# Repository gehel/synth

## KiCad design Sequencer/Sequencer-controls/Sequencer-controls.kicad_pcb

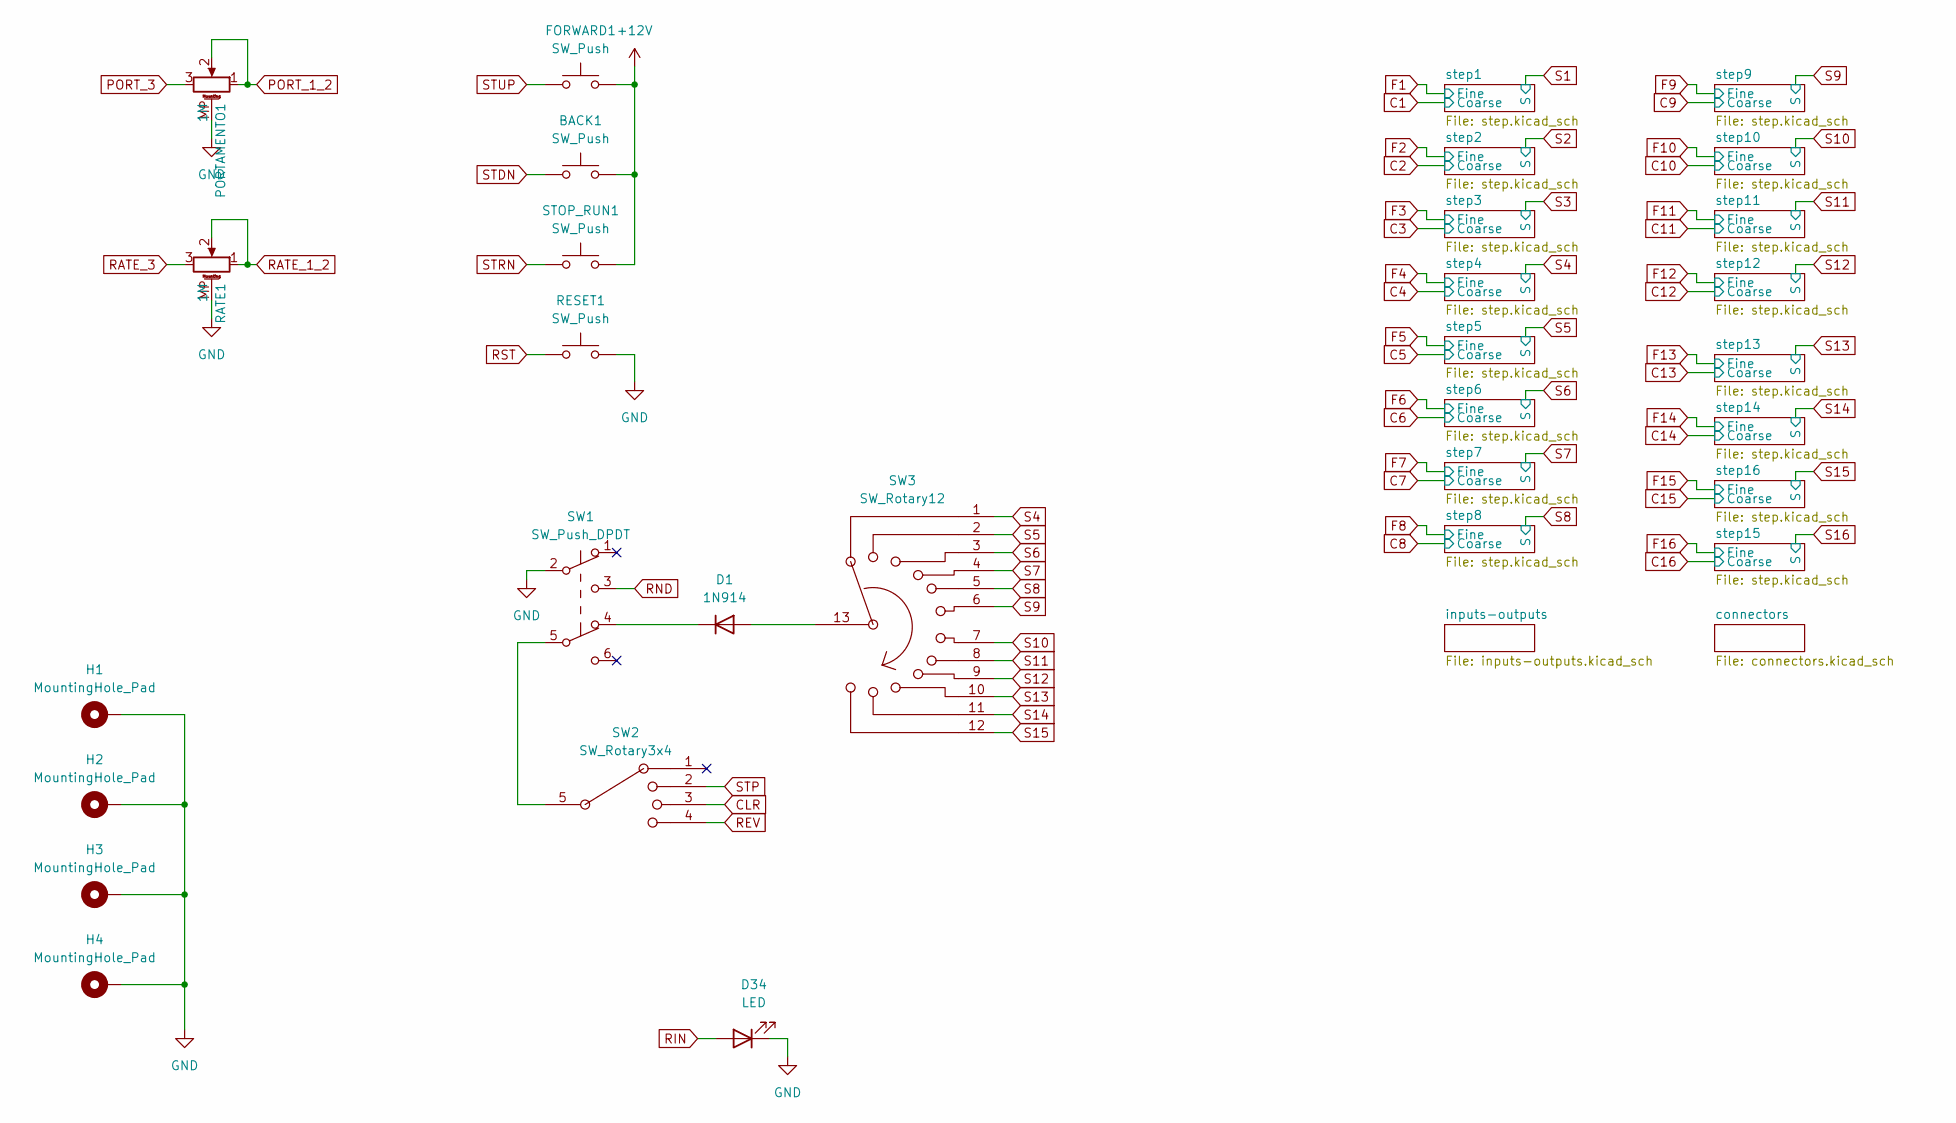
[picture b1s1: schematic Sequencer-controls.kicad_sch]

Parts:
BACK1: SW_Push; SW_PUSH_6mm
D1: 1N914; D_DO-35_SOD27_P7.62mm_Horizontal
D34: LED; LED_D3.0mm
FORWARD1: SW_Push; SW_PUSH_6mm
H1, H2, H3, H4: MountingHole_Pad; MountingHole_3.2mm_M3_Pad
PORTAMENTO1: 1M; Potentiometer_Bourns_PTV09A-1_Single_Vertical
RATE1: 1M; Potentiometer_Bourns_PTV09A-1_Single_Vertical
RESET1: SW_Push; SW_PUSH_6mm
STOP_RUN1: SW_Push; SW_PUSH_6mm
SW1: SW_Push_DPDT; ToggleSwitch_MTS-202_DPDT
SW2: SW_Rotary3x4; rotary_switch_3P4T
SW3: SW_Rotary12; rotary_switch_1P12T

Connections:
+12V: BACK1.2, FORWARD1.2, STOP_RUN1.2; also elsewhere on the board
CLR: SW2.3; also elsewhere on the board
GND: D34.1 (K), H1.1, H2.1, H3.1, H4.1, PORTAMENTO1.MP (MountPin), RATE1.MP (MountPin), RESET1.2, SW1.2 (B); also elsewhere on the board
unnamed: D1.2 (A), SW3.13
unnamed: D1.1 (K), SW1.4 (A)
unnamed: SW1.5 (B), SW2.5
PORT_1_2: PORTAMENTO1.1, PORTAMENTO1.2; also elsewhere on the board
PORT_3: PORTAMENTO1.3; also elsewhere on the board
RATE_1_2: RATE1.1, RATE1.2; also elsewhere on the board
RATE_3: RATE1.3; also elsewhere on the board
REV: SW2.4; also elsewhere on the board
RIN: D34.2 (A); also elsewhere on the board
RND: SW1.3 (C); also elsewhere on the board
RST: RESET1.1; also elsewhere on the board
S4: SW3.1; also elsewhere on the board
S5: SW3.2; also elsewhere on the board
S6: SW3.3; also elsewhere on the board
S7: SW3.4; also elsewhere on the board
S8: SW3.5; also elsewhere on the board
S9: SW3.6; also elsewhere on the board
S10: SW3.7; also elsewhere on the board
S11: SW3.8; also elsewhere on the board
S12: SW3.9; also elsewhere on the board
S13: SW3.10; also elsewhere on the board
S14: SW3.11; also elsewhere on the board
STDN: BACK1.1; also elsewhere on the board
STP: SW2.2; also elsewhere on the board
STRN: STOP_RUN1.1; also elsewhere on the board
STUP: FORWARD1.1; also elsewhere on the board

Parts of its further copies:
D11: LED; LED_D3.0mm

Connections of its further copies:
CBUS: D11.1 (K); also elsewhere on the board
S5: D11.2 (A); also elsewhere on the board

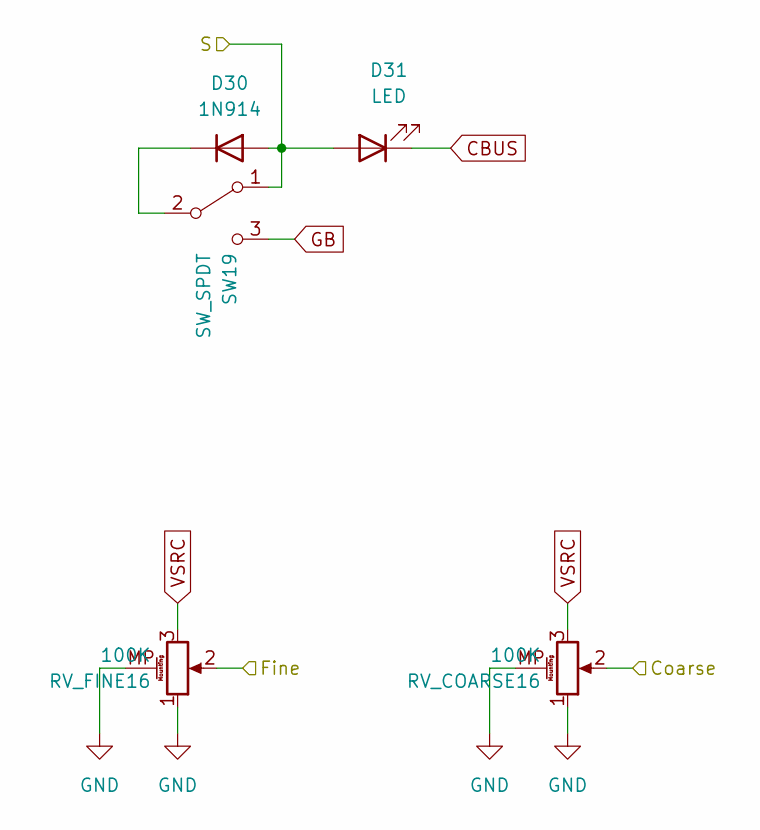
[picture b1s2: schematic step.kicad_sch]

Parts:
D30: 1N914; D_DO-35_SOD27_P7.62mm_Horizontal
D31: LED; LED_D3.0mm
RV_COARSE16: 100K; Potentiometer_Bourns_PTV09A-1_Single_Vertical
RV_FINE16: 100K; Potentiometer_Bourns_PTV09A-1_Single_Vertical
SW19: SW_SPDT; ToggleSwitch_MTS-102_SPDT

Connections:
C16: RV_COARSE16.2; also elsewhere on the board
CBUS: D31.1 (K); also elsewhere on the board
F16: RV_FINE16.2; also elsewhere on the board
GB: SW19.3 (C); also elsewhere on the board
GND: RV_COARSE16.1, RV_COARSE16.MP (MountPin), RV_FINE16.1, RV_FINE16.MP (MountPin); also elsewhere on the board
VSRC: RV_COARSE16.3, RV_FINE16.3; also elsewhere on the board

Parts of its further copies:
D2, D4, D6, D8, D10, D12, D14, D16, D18, D20, D22, D24, D26, D28, D32: 1N914; D_DO-35_SOD27_P7.62mm_Horizontal
D3, D5, D7, D9, D11, D13, D15, D17, D19, D21, D23, D25, D27, D29, D33: LED; LED_D3.0mm
RV_COARSE1, RV_COARSE2, RV_COARSE3, RV_COARSE4, RV_COARSE5, RV_COARSE6, RV_COARSE7, RV_COARSE8, RV_COARSE9, RV_COARSE10, RV_COARSE11, RV_COARSE12, RV_COARSE13, RV_COARSE14, RV_COARSE15: 100K; Potentiometer_Bourns_PTV09A-1_Single_Vertical
RV_FINE1, RV_FINE2, RV_FINE3, RV_FINE4, RV_FINE5, RV_FINE6, RV_FINE7, RV_FINE8, RV_FINE9, RV_FINE10, RV_FINE11, RV_FINE12, RV_FINE13, RV_FINE14, RV_FINE15: 100K; Potentiometer_Bourns_PTV09A-1_Single_Vertical
SW4, SW5, SW6, SW7, SW8, SW9, SW10, SW11, SW12, SW13, SW14, SW15, SW16, SW17, SW18: SW_SPDT; ToggleSwitch_MTS-102_SPDT

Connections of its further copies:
C1: RV_COARSE1.2; also elsewhere on the board
C2: RV_COARSE2.2; also elsewhere on the board
C3: RV_COARSE3.2; also elsewhere on the board
C4: RV_COARSE4.2; also elsewhere on the board
C5: RV_COARSE5.2; also elsewhere on the board
C6: RV_COARSE6.2; also elsewhere on the board
C7: RV_COARSE7.2; also elsewhere on the board
C8: RV_COARSE8.2; also elsewhere on the board
C9: RV_COARSE9.2; also elsewhere on the board
C10: RV_COARSE10.2; also elsewhere on the board
C11: RV_COARSE11.2; also elsewhere on the board
C12: RV_COARSE12.2; also elsewhere on the board
C13: RV_COARSE13.2; also elsewhere on the board
C14: RV_COARSE14.2; also elsewhere on the board
C15: RV_COARSE15.2; also elsewhere on the board
CBUS: D3.1 (K), D5.1 (K), D7.1 (K), D9.1 (K), D11.1 (K), D13.1 (K), D15.1 (K), D17.1 (K), D19.1 (K), D21.1 (K), D23.1 (K), D25.1 (K), D27.1 (K), D29.1 (K), D33.1 (K); also elsewhere on the board
F1: RV_FINE1.2; also elsewhere on the board
F2: RV_FINE2.2; also elsewhere on the board
F3: RV_FINE3.2; also elsewhere on the board
F4: RV_FINE4.2; also elsewhere on the board
F5: RV_FINE5.2; also elsewhere on the board
F6: RV_FINE6.2; also elsewhere on the board
F7: RV_FINE7.2; also elsewhere on the board
F8: RV_FINE8.2; also elsewhere on the board
F9: RV_FINE9.2; also elsewhere on the board
F10: RV_FINE10.2; also elsewhere on the board
F11: RV_FINE11.2; also elsewhere on the board
F12: RV_FINE12.2; also elsewhere on the board
F13: RV_FINE13.2; also elsewhere on the board
F14: RV_FINE14.2; also elsewhere on the board
F15: RV_FINE15.2; also elsewhere on the board
GB: SW4.3 (C), SW5.3 (C), SW6.3 (C), SW7.3 (C), SW8.3 (C), SW9.3 (C), SW10.3 (C), SW11.3 (C), SW12.3 (C), SW13.3 (C), SW14.3 (C), SW15.3 (C), SW16.3 (C), SW17.3 (C), SW18.3 (C); also elsewhere on the board
GND: RV_COARSE1.1, RV_COARSE1.MP (MountPin), RV_COARSE2.1, RV_COARSE2.MP (MountPin), RV_COARSE3.1, RV_COARSE3.MP (MountPin), RV_COARSE4.1, RV_COARSE4.MP (MountPin), RV_COARSE5.1, RV_COARSE5.MP (MountPin), RV_COARSE6.1, RV_COARSE6.MP (MountPin), RV_COARSE7.1, RV_COARSE7.MP (MountPin), RV_COARSE8.1, RV_COARSE8.MP (MountPin), RV_COARSE9.1, RV_COARSE9.MP (MountPin), RV_COARSE10.1, RV_COARSE10.MP (MountPin), RV_COARSE11.1, RV_COARSE11.MP (MountPin), RV_COARSE12.1, RV_COARSE12.MP (MountPin), RV_COARSE13.1, RV_COARSE13.MP (MountPin), RV_COARSE14.1, RV_COARSE14.MP (MountPin), RV_COARSE15.1, RV_COARSE15.MP (MountPin), RV_FINE1.1, RV_FINE1.MP (MountPin), RV_FINE2.1, RV_FINE2.MP (MountPin), RV_FINE3.1, RV_FINE3.MP (MountPin), RV_FINE4.1, RV_FINE4.MP (MountPin), RV_FINE5.1, RV_FINE5.MP (MountPin), RV_FINE6.1, RV_FINE6.MP (MountPin), RV_FINE7.1, RV_FINE7.MP (MountPin), RV_FINE8.1, RV_FINE8.MP (MountPin), RV_FINE9.1, RV_FINE9.MP (MountPin), RV_FINE10.1, RV_FINE10.MP (MountPin), RV_FINE11.1, RV_FINE11.MP (MountPin), RV_FINE12.1, RV_FINE12.MP (MountPin), RV_FINE13.1, RV_FINE13.MP (MountPin), RV_FINE14.1, RV_FINE14.MP (MountPin), RV_FINE15.1, RV_FINE15.MP (MountPin); also elsewhere on the board
unnamed: D2.1 (K), SW4.2 (B)
unnamed: D4.1 (K), SW5.2 (B)
unnamed: D6.1 (K), SW6.2 (B)
unnamed: D8.1 (K), SW7.2 (B)
unnamed: D10.1 (K), SW8.2 (B)
unnamed: D12.1 (K), SW9.2 (B)
unnamed: D14.1 (K), SW10.2 (B)
unnamed: D16.1 (K), SW11.2 (B)
unnamed: D18.1 (K), SW12.2 (B)
unnamed: D20.1 (K), SW13.2 (B)
unnamed: D22.1 (K), SW14.2 (B)
unnamed: D24.1 (K), SW15.2 (B)
unnamed: D26.1 (K), SW16.2 (B)
unnamed: D28.1 (K), SW17.2 (B)
S1: D2.2 (A), D3.2 (A), SW4.1 (A); also elsewhere on the board
S2: D4.2 (A), D5.2 (A), SW5.1 (A); also elsewhere on the board
S3: D6.2 (A), D7.2 (A), SW6.1 (A); also elsewhere on the board
S4: D8.2 (A), D9.2 (A), SW7.1 (A); also elsewhere on the board
S5: D10.2 (A), D11.2 (A), SW8.1 (A); also elsewhere on the board
S6: D12.2 (A), D13.2 (A), SW9.1 (A); also elsewhere on the board
S7: D14.2 (A), D15.2 (A), SW10.1 (A); also elsewhere on the board
S8: D16.2 (A), D17.2 (A), SW11.1 (A); also elsewhere on the board
S9: D18.2 (A), D19.2 (A), SW12.1 (A); also elsewhere on the board
S10: D20.2 (A), D21.2 (A), SW13.1 (A); also elsewhere on the board
S11: D22.2 (A), D23.2 (A), SW14.1 (A); also elsewhere on the board
S12: D24.2 (A), D25.2 (A), SW15.1 (A); also elsewhere on the board
S13: D26.2 (A), D27.2 (A), SW16.1 (A); also elsewhere on the board
S14: D28.2 (A), D29.2 (A), SW17.1 (A); also elsewhere on the board
VSRC: RV_COARSE1.3, RV_COARSE2.3, RV_COARSE3.3, RV_COARSE4.3, RV_COARSE5.3, RV_COARSE6.3, RV_COARSE7.3, RV_COARSE8.3, RV_COARSE9.3, RV_COARSE10.3, RV_COARSE11.3, RV_COARSE12.3, RV_COARSE13.3, RV_COARSE14.3, RV_COARSE15.3, RV_FINE1.3, RV_FINE2.3, RV_FINE3.3, RV_FINE4.3, RV_FINE5.3, RV_FINE6.3, RV_FINE7.3, RV_FINE8.3, RV_FINE9.3, RV_FINE10.3, RV_FINE11.3, RV_FINE12.3, RV_FINE13.3, RV_FINE14.3, RV_FINE15.3; also elsewhere on the board

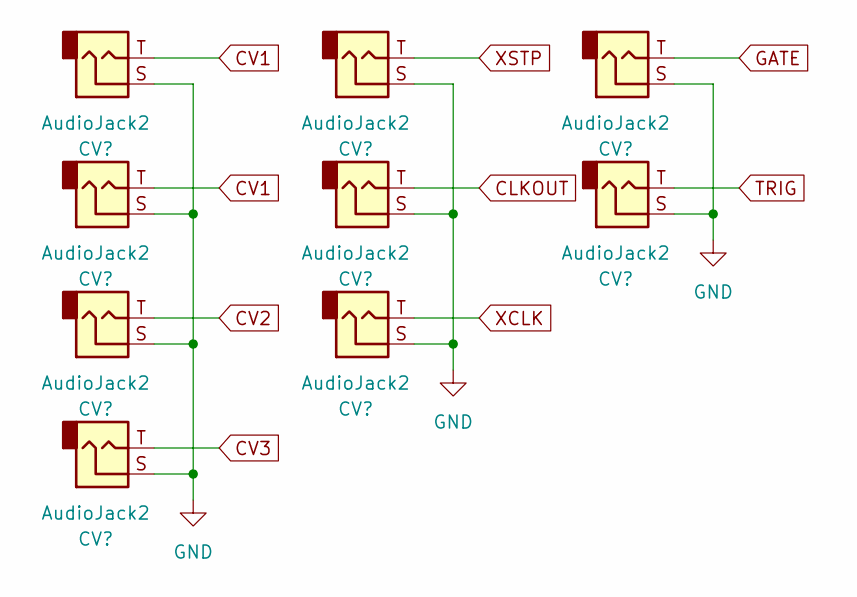
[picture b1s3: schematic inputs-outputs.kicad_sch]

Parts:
CLKOUT1: AudioJack2; Jack_3.5mm_QingPu_WQP-PJ398SM_Vertical_CircularHoles
CV1, CV2, CV3, CV4: AudioJack2; Jack_3.5mm_QingPu_WQP-PJ398SM_Vertical_CircularHoles
GATE1: AudioJack2; Jack_3.5mm_QingPu_WQP-PJ398SM_Vertical_CircularHoles
TRIG1: AudioJack2; Jack_3.5mm_QingPu_WQP-PJ398SM_Vertical_CircularHoles
XCLK1: AudioJack2; Jack_3.5mm_QingPu_WQP-PJ398SM_Vertical_CircularHoles
XSTP1: AudioJack2; Jack_3.5mm_QingPu_WQP-PJ398SM_Vertical_CircularHoles

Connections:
CLKOUT: CLKOUT1.T; also elsewhere on the board
CV1: CV1.T, CV2.T; also elsewhere on the board
CV2: CV3.T; also elsewhere on the board
CV3: CV4.T; also elsewhere on the board
GATE: GATE1.T; also elsewhere on the board
GND: CLKOUT1.S, CV1.S, CV2.S, CV3.S, CV4.S, GATE1.S, TRIG1.S, XCLK1.S, XSTP1.S; also elsewhere on the board
TRIG: TRIG1.T; also elsewhere on the board
XCLK: XCLK1.T; also elsewhere on the board
XSTP: XSTP1.T; also elsewhere on the board

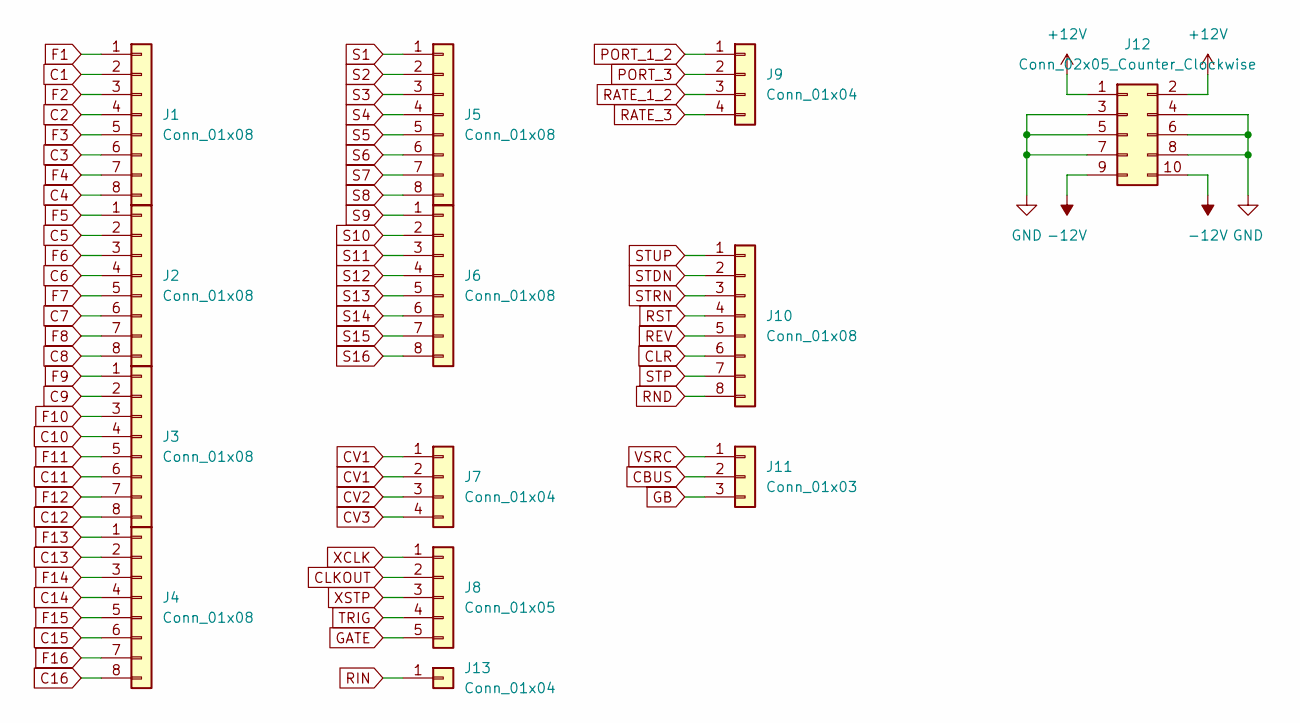
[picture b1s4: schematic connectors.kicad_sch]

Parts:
J1, J2, J3, J4, J5, J6, J10: Conn_01x08; PinHeader_1x08_P2.54mm_Vertical
J7, J9: Conn_01x04; PinHeader_1x04_P2.54mm_Vertical
J8: Conn_01x05; PinHeader_1x05_P2.54mm_Vertical
J11: Conn_01x03; PinHeader_1x03_P2.54mm_Vertical
J12: Conn_02x05_Counter_Clockwise; PinHeader_2x05_P2.54mm_Vertical
J13: Conn_01x04; PinHeader_1x01_P2.54mm_Vertical

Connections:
+12V: J12.1, J12.2; also elsewhere on the board
-12V: J12.9, J12.10
C1: J1.2; also elsewhere on the board
C2: J1.4; also elsewhere on the board
C3: J1.6; also elsewhere on the board
C4: J1.8; also elsewhere on the board
C5: J2.2; also elsewhere on the board
C6: J2.4; also elsewhere on the board
C7: J2.6; also elsewhere on the board
C8: J2.8; also elsewhere on the board
C9: J3.2; also elsewhere on the board
C10: J3.4; also elsewhere on the board
C11: J3.6; also elsewhere on the board
C12: J3.8; also elsewhere on the board
C13: J4.2; also elsewhere on the board
C14: J4.4; also elsewhere on the board
C15: J4.6; also elsewhere on the board
C16: J4.8; also elsewhere on the board
CBUS: J11.2; also elsewhere on the board
CLKOUT: J8.2; also elsewhere on the board
CLR: J10.6; also elsewhere on the board
CV1: J7.1, J7.2; also elsewhere on the board
CV2: J7.3; also elsewhere on the board
CV3: J7.4; also elsewhere on the board
F1: J1.1; also elsewhere on the board
F2: J1.3; also elsewhere on the board
F3: J1.5; also elsewhere on the board
F4: J1.7; also elsewhere on the board
F5: J2.1; also elsewhere on the board
F6: J2.3; also elsewhere on the board
F7: J2.5; also elsewhere on the board
F8: J2.7; also elsewhere on the board
F9: J3.1; also elsewhere on the board
F10: J3.3; also elsewhere on the board
F11: J3.5; also elsewhere on the board
F12: J3.7; also elsewhere on the board
F13: J4.1; also elsewhere on the board
F14: J4.3; also elsewhere on the board
F15: J4.5; also elsewhere on the board
F16: J4.7; also elsewhere on the board
GATE: J8.5; also elsewhere on the board
GB: J11.3; also elsewhere on the board
GND: J12.3, J12.4, J12.5, J12.6, J12.7, J12.8; also elsewhere on the board
PORT_1_2: J9.1; also elsewhere on the board
PORT_3: J9.2; also elsewhere on the board
RATE_1_2: J9.3; also elsewhere on the board
RATE_3: J9.4; also elsewhere on the board
REV: J10.5; also elsewhere on the board
RND: J10.8; also elsewhere on the board
RST: J10.4; also elsewhere on the board
S1: J5.1; also elsewhere on the board
S2: J5.2; also elsewhere on the board
S3: J5.3; also elsewhere on the board
S4: J5.4; also elsewhere on the board
S5: J5.5; also elsewhere on the board
S6: J5.6; also elsewhere on the board
S7: J5.7; also elsewhere on the board
S8: J5.8; also elsewhere on the board
S9: J6.1; also elsewhere on the board
S10: J6.2; also elsewhere on the board
S11: J6.3; also elsewhere on the board
S12: J6.4; also elsewhere on the board
S13: J6.5; also elsewhere on the board
S14: J6.6; also elsewhere on the board
STDN: J10.2; also elsewhere on the board
STP: J10.7; also elsewhere on the board
STRN: J10.3; also elsewhere on the board
STUP: J10.1; also elsewhere on the board
TRIG: J8.4; also elsewhere on the board
VSRC: J11.1; also elsewhere on the board
XCLK: J8.1; also elsewhere on the board
XSTP: J8.3; also elsewhere on the board

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
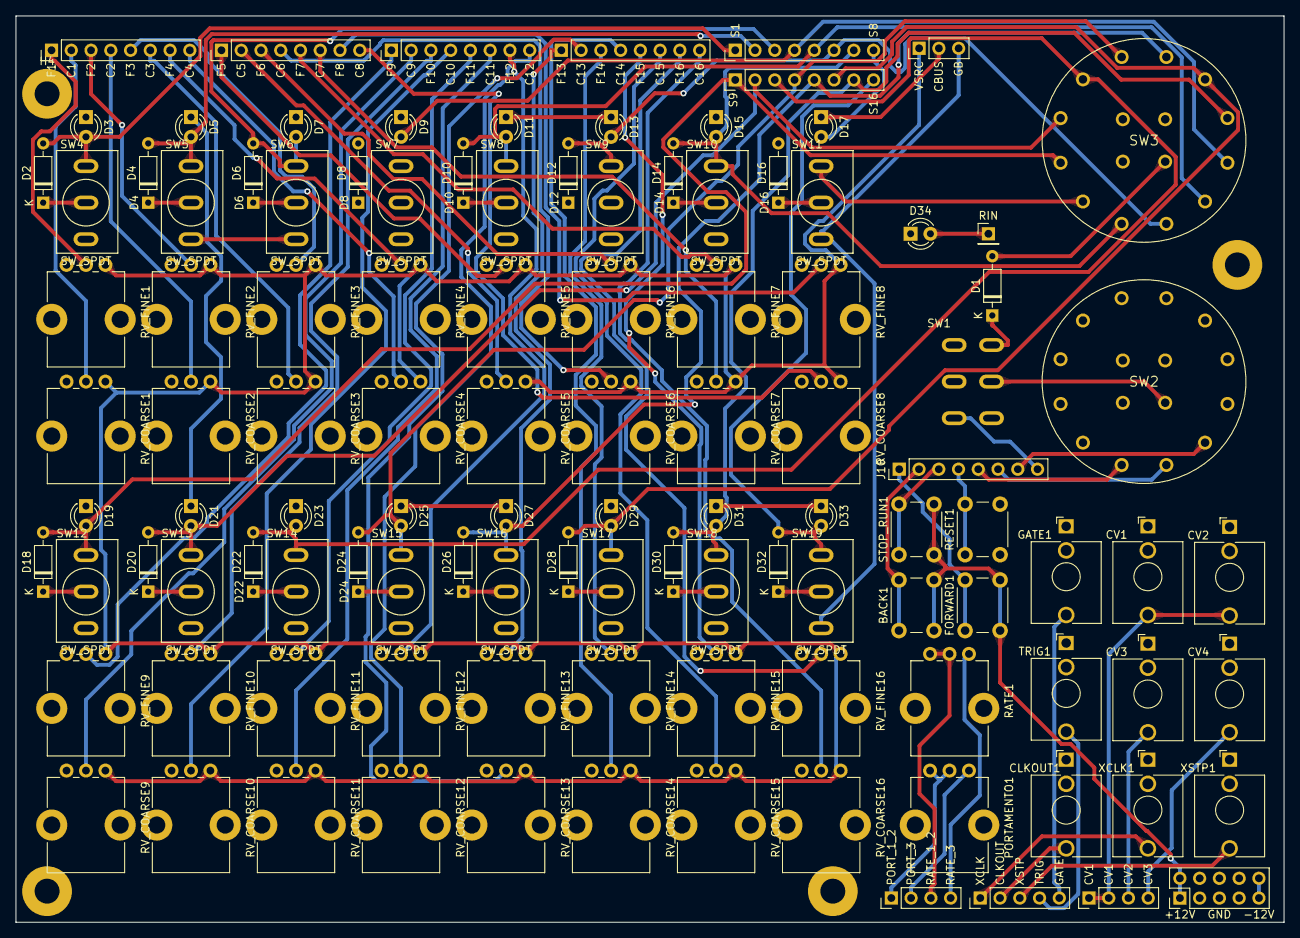
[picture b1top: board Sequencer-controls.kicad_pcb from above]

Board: 4 copper layers, 163.0 x 116.5 mm, 117 parts (0 on the bottom side), 94 nets.

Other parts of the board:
RIN: Conn_01x04; PinHeader_1x01_P2.54mm_Vertical

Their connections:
RIN: RIN.1; also elsewhere on the board

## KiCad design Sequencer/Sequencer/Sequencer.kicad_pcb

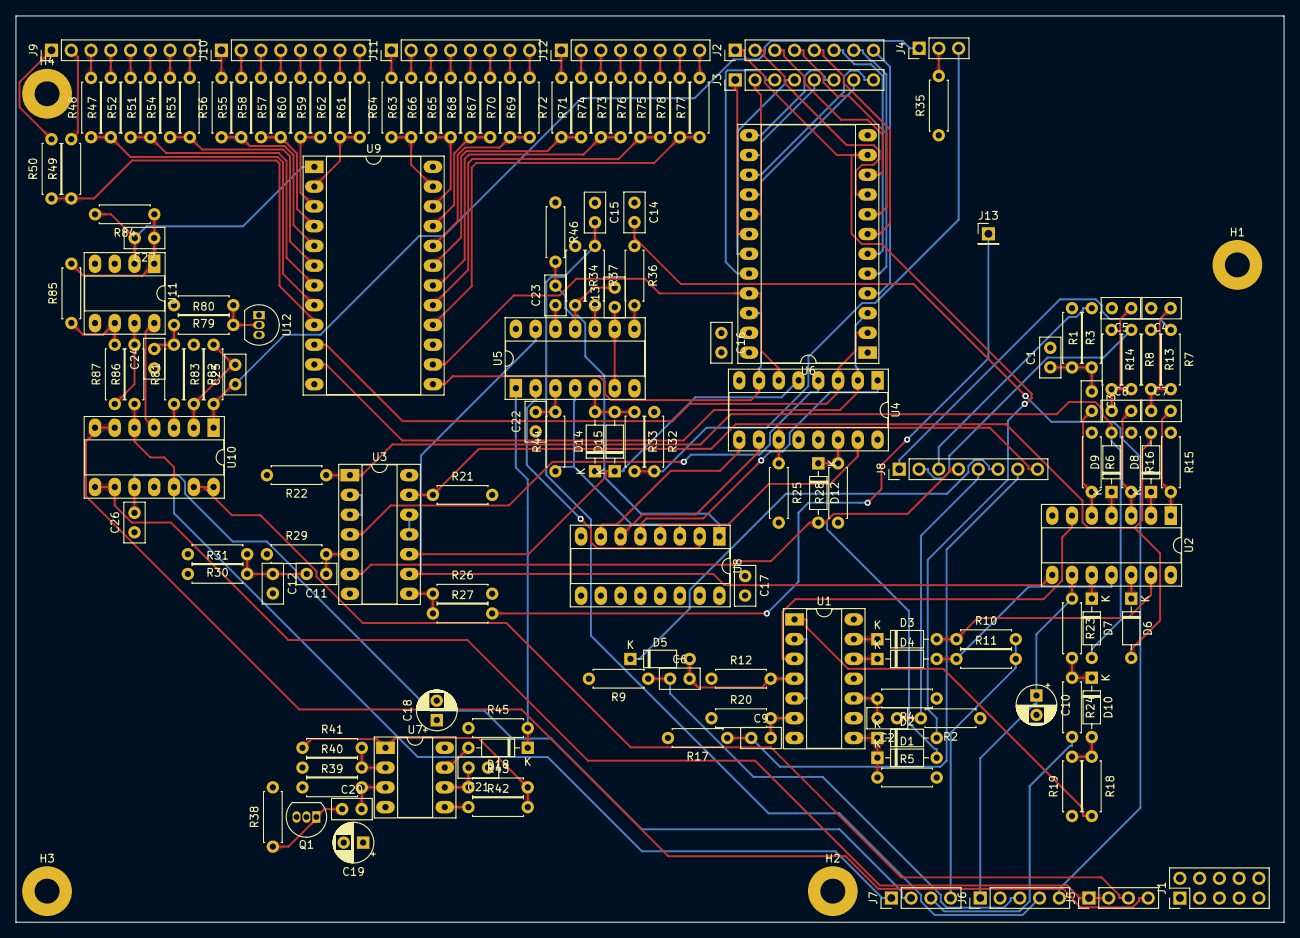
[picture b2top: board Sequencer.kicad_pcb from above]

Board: 4 copper layers, 163.0 x 116.5 mm, 158 parts (0 on the bottom side), 157 nets.

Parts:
C1, C4, C5, C6, C9, C12, C20, C21: 10nF; C_Disc_D5.0mm_W2.5mm_P2.50mm
C2, C3, C7, C8, C11: 20nF; C_Disc_D5.0mm_W2.5mm_P2.50mm
C10: 1uF; CP_Radial_D5.0mm_P2.50mm
C13, C14, C15, C22: 1nF; C_Disc_D5.0mm_W2.5mm_P2.50mm
C16, C17, C24, C26: 100nF; C_Disc_D5.0mm_W2.5mm_P2.50mm
C18, C19: 10uF; CP_Radial_D5.0mm_P2.50mm
C23: 100pF; C_Disc_D5.0mm_W2.5mm_P2.50mm
C25, C27: 470pF; C_Disc_D5.0mm_W2.5mm_P2.50mm
D1, D2, D3, D4, D5, D6, D7, D8, D9, D10, D12, D14, D15, D18: 1N914; D_DO-35_SOD27_P7.62mm_Horizontal
H1, H2, H3, H4: MountingHole_Pad; MountingHole_3.2mm_M3_Pad
J1: Conn_02x05_Odd_Even; PinHeader_2x05_P2.54mm_Vertical
J2, J3, J8, J9, J10, J11, J12: Conn_01x08; PinHeader_1x08_P2.54mm_Vertical
J4: Conn_01x03; PinHeader_1x03_P2.54mm_Vertical
J5, J7: Conn_01x04; PinHeader_1x04_P2.54mm_Vertical
J6: Conn_01x05; PinHeader_1x05_P2.54mm_Vertical
J13: Conn_01x04; PinHeader_1x01_P2.54mm_Vertical
Q1: 2N3904; TO-92_Inline
R1, R5, R7, R8, R10, R11, R31, R79, R85, R87: 10K; R_Axial_DIN0207_L6.3mm_D2.5mm_P7.62mm_Horizontal
R2, R4, R6, R15, R16, R29: 220K; R_Axial_DIN0207_L6.3mm_D2.5mm_P7.62mm_Horizontal
R3, R13, R14, R30: 680K; R_Axial_DIN0207_L6.3mm_D2.5mm_P7.62mm_Horizontal
R9, R12, R17, R20, R33, R34, R42, R47, R49, R51, R53, R55, R57, R59, R61, R63, R65, R67, R69, R71, R73, R75, R77, R82, R84: 100K; R_Axial_DIN0207_L6.3mm_D2.5mm_P7.62mm_Horizontal
R18, R26, R36, R37: 1K; R_Axial_DIN0207_L6.3mm_D2.5mm_P7.62mm_Horizontal
R19: 3.9K; R_Axial_DIN0207_L6.3mm_D2.5mm_P7.62mm_Horizontal
R21, R22, R25, R28, R80, R81: 47K; R_Axial_DIN0207_L6.3mm_D2.5mm_P7.62mm_Horizontal
R23: 6.2K; R_Axial_DIN0207_L6.3mm_D2.5mm_P7.62mm_Horizontal
R24: 20K; R_Axial_DIN0207_L6.3mm_D2.5mm_P7.62mm_Horizontal
R27, R35: 3K; R_Axial_DIN0207_L6.3mm_D2.5mm_P7.62mm_Horizontal
R32, R40, R45, R46: 4.7K; R_Axial_DIN0207_L6.3mm_D2.5mm_P7.62mm_Horizontal
R38, R39, R48, R50, R52, R54, R56, R58, R60, R62, R64, R66, R68, R70, R72, R74, R76, R78: 2M; R_Axial_DIN0207_L6.3mm_D2.5mm_P7.62mm_Horizontal
R41: 4.7M; R_Axial_DIN0207_L6.3mm_D2.5mm_P7.62mm_Horizontal
R43, R44: 1M; R_Axial_DIN0207_L6.3mm_D2.5mm_P7.62mm_Horizontal
R83: 200K; R_Axial_DIN0207_L6.3mm_D2.5mm_P7.62mm_Horizontal
R86: 22R; R_Axial_DIN0207_L6.3mm_D2.5mm_P7.62mm_Horizontal
U1: 4013; DIP-14_W7.62mm_Socket_LongPads
U2, U3, U5: 40106; DIP-14_W7.62mm_Socket_LongPads
U4: 40193; DIP-16_W7.62mm_Socket_LongPads
U6: 4514; DIP-24_W15.24mm_Socket_LongPads
U7, U11: TL072; DIP-8_W7.62mm_Socket_LongPads
U8: CD4094; DIP-16_W7.62mm_Socket_LongPads
U9: CD74HC4067M; DIP-24_W15.24mm_Socket_LongPads
U10: TL074; DIP-14_W7.62mm_Socket_LongPads
U12: LM285Z-ADJ; TO-92_Inline

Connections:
+12V: C16.2, C17.2, C18.1, J1.1, J1.2, R21.2, R22.2, R25.2, R29.1, R30.2, R34.1, R38.2, R79.2, U1.14 (VDD), U2.14 (VDD), U3.14 (VDD), U4.16 (VDD), U5.14 (VDD), U6.1 (EL), U6.24 (Vdd), U7.8 (V+), U8.15 (ENA), U8.16 (VDD), U9.24 (VCC), U10.4 (V+), U11.8 (V+)
-12V: C19.2, J1.9, J1.10, Q1.2 (B), U7.4 (V-), U10.11 (V-), U11.4 (V-)
C1: J9.2, R49.2
C2: J9.4, R47.2
C3: J9.6, R51.2
C4: J9.8, R53.2
C5: J10.2, R55.2
C6: J10.4, R57.2
C7: J10.6, R59.2
C8: J10.8, R61.2
C9: J11.2, R63.2
C10: J11.4, R65.2
C11: J11.6, R67.2
C12: J11.8, R69.2
C13: J12.2, R71.2
C14: J12.4, R73.2
C15: J12.6, R75.2
C16: J12.8, R77.2
CBUS: J4.2, R35.2
CLK: J7.4, R10.2, R11.2, U2.8, U3.9, U5.13
CLR: D5.1 (K), J8.6
CV1: J5.1, J5.2, U10.8, U10.9 (-)
CV2: J5.3, U10.13 (-), U10.14
CV3: J5.4, U10.6 (-), U10.7
DA: U4.15 (P0), U8.4 (Q1)
DB: U4.1, U8.5 (Q2)
DC: U4.10 (P2), U8.6 (Q3)
DD: U4.9 (P3), U8.7 (Q4)
DOWN: U3.4, U4.4 (DOWN)
F1: J9.1, R50.2
F2: J9.3, R48.2
F3: J9.5, R52.2
F4: J9.7, R54.2
F5: J10.1, R56.2
F6: J10.3, R58.2
F7: J10.5, R60.2
F8: J10.7, R62.2
F9: J11.1, R64.2
F10: J11.3, R66.2
F11: J11.5, R68.2
F12: J11.7, R70.2
F13: J12.1, R72.2
F14: J12.3, R74.2
F15: J12.5, R76.2
F16: J12.7, R78.2
FR1: R49.1, R50.1, U9.9 (I0)
FR2: R47.1, R48.1, U9.8 (I1)
FR3: R51.1, R52.1, U9.7 (I2)
FR4: R53.1, R54.1, U9.6 (I3)
FR5: R55.1, R56.1, U9.5 (I4)
FR6: R57.1, R58.1, U9.4 (I5)
FR7: R59.1, R60.1, U9.3 (I6)
FR8: R61.1, R62.1, U9.2 (I7)
FR9: R63.1, R64.1, U9.23 (I8)
FR10: R65.1, R66.1, U9.22 (I9)
FR11: R67.1, R68.1, U9.21 (I10)
FR12: R69.1, R70.1, U9.20 (I11)
FR13: R71.1, R72.1, U9.19 (I12)
FR14: R73.1, R74.1, U9.18 (I13)
FR15: R75.1, R76.1, U9.17 (I14)
FR16: R77.1, R78.1, U9.16 (I15)
FWD: D2.2 (A), J2.1, U6.11 (Q0)
GATE: C14.2, J6.5, R36.1
GB: J4.3, R32.2, R33.2
GND: C1.2, C4.2, C5.2, C10.2, C12.2, C14.1, C15.1, C16.1, C17.1, C18.2, C19.1, C21.1, C22.1, C24.1, C26.1, H1.1, H2.1, H3.1, H4.1, J1.3, J1.4, J1.5, J1.6, J1.7, J1.8, R2.1, R3.1, R4.1, R5.2, R6.1, R9.2, R12.1, R13.1, R14.1, R15.1, R16.1, R17.2, R19.1, R20.1, R28.1, R32.1, R35.1, R39.1, R40.1, R45.1, R46.1, R82.1, U1.7 (VSS), U1.9 (D), U1.11 (C), U2.7 (VSS), U3.7 (VSS), U4.8 (VSS), U5.7 (VSS), U6.12 (Vss), U6.23 (~EN), U8.8 (VSS), U9.12 (GND), U9.15 (~E), U11.3 (+), U11.5 (+), U12.3 (A)
unnamed: C1.1, C3.1, R1.1, R3.2
unnamed: C3.2, R6.2, U2.5
unnamed: C4.1, C7.1, R7.2, R13.2
unnamed: C5.1, C8.1, R8.2, R14.2
unnamed: C7.2, R15.2, U2.1
unnamed: C8.2, R16.2, U2.3
unnamed: C11.1, R29.2, U3.5
unnamed: C11.2, C12.1, R30.1, R31.2
unnamed: C13.1, U5.6, U5.9
unnamed: C13.2, R34.2, U5.11
unnamed: C22.2, R44.2, U5.3
unnamed: C23.1, U5.12
unnamed: C24.2, R80.1, R81.2
unnamed: C27.1, R84.1, R85.2, U11.1
unnamed: D1.1 (K), D2.1 (K), R5.1, U1.8 (S)
unnamed: D3.2 (A), R10.1, U2.13
unnamed: D3.1 (K), U1.13 (Q)
unnamed: D4.2 (A), R11.1, U2.11
unnamed: D4.1 (K), U1.12 (~Q)
unnamed: C6.2, D5.2 (A), R12.2, U1.4 (R)
unnamed: D6.2 (A), D8.2 (A), R21.1, U3.13
unnamed: D6.1 (K), U2.12
unnamed: D7.2 (A), D9.2 (A), R22.1, U3.1
unnamed: D7.1 (K), U2.10
unnamed: D8.1 (K), U2.2
unnamed: D9.1 (K), U2.4
unnamed: D10.2 (A), R18.1, R19.2
unnamed: D10.1 (K), R23.2, R24.1
unnamed: D12.1 (K), R28.2, U4.14 (MR)
unnamed: D14.2 (A), D15.2 (A), R33.1, U5.5
unnamed: D18.2 (A), U7.7
unnamed: D18.1 (K), R45.2, U5.1
unnamed: C20.1, Q1.1 (E), R38.1
unnamed: R26.1, R27.1, U3.8
unnamed: R36.2, U5.8
unnamed: R37.2, U5.10
unnamed: R41.1, R42.2, R43.2, U7.1
unnamed: R86.2, R87.1, U11.7
unnamed: U1.3 (C), U2.6
unnamed: U1.2 (~Q), U1.5 (D)
unnamed: R18.2, U1.1 (Q)
unnamed: C9.2, R20.2, U1.6 (S)
unnamed: C2.2, R4.2, U1.10 (R)
unnamed: U3.2, U3.3
unnamed: U3.11, U3.12
unnamed: C20.2, R39.2, U7.3 (+)
unnamed: R40.2, R41.2, U7.2 (-)
unnamed: R42.1, U7.5 (+)
unnamed: C21.2, R43.1, U7.6 (-)
unnamed: R44.1, U5.4, U8.3 (CLK)
unnamed: U5.2, U8.2 (DATA)
unnamed: C23.2, R46.2, U8.1 (STROBE)
unnamed: R81.1, U10.3 (+)
unnamed: C25.2, R82.2, R83.2, U10.2 (-)
unnamed: C27.2, R84.2, U9.1 (COM), U11.2 (-)
unnamed: R85.1, R87.2, U11.6 (-)
unnamed: R79.1, R80.2, U12.2 (K)
PORT_1_2: J7.1, R86.1, U10.5 (+), U10.12 (+)
PORT_3: C26.2, J7.2, U10.10 (+)
QA: U4.3 (Q0), U6.2 (A0), U9.10 (S0)
QB: U4.2 (Q1), U6.3 (A1), U9.11 (S1)
QC: U4.6 (Q2), U6.21 (A2), U9.14 (S2)
QD: U4.7 (Q3), U6.22 (A3), U9.13 (S3)
RATE_1_2: J7.3, R24.2
REV: C2.1, J8.5, R2.2
RIN: J13.1, R27.2
RND: J8.8, R25.1, U4.11 (LOAD)
RST: D1.2 (A), D12.2 (A), J8.4, U3.6
S2: J2.2, U6.9 (Q1)
S3: J2.3, U6.10 (Q2)
S4: J2.4, U6.8 (Q3)
S5: J2.5, U6.7 (Q4)
S6: J2.6, U6.6 (Q5)
S7: J2.7, U6.5 (Q6)
S8: J2.8, U6.4 (Q7)
S9: J3.1, U6.18 (Q8)
S10: J3.2, U6.17 (Q9)
S11: J3.3, U6.20 (Q10)
S12: J3.4, U6.19 (Q11)
S13: J3.5, U6.14 (Q12)
S14: J3.6, U6.13 (Q13)
S15: J3.7, U6.16 (Q14)
S16: J3.8, U6.15 (Q15)
STDN: J8.2, R8.1
STP: C9.1, J8.7, R17.1
STRN: J8.3, R1.2
STUP: J8.1, R7.1
TRIG: C15.2, J6.4, R37.1
UP: D15.1 (K), U3.10, U4.5 (UP)
VSRC: C25.1, J4.1, R83.1, U10.1
XCLK: C10.1, J6.1, R23.1, U2.9
XSTP: C6.1, J6.3, R9.1

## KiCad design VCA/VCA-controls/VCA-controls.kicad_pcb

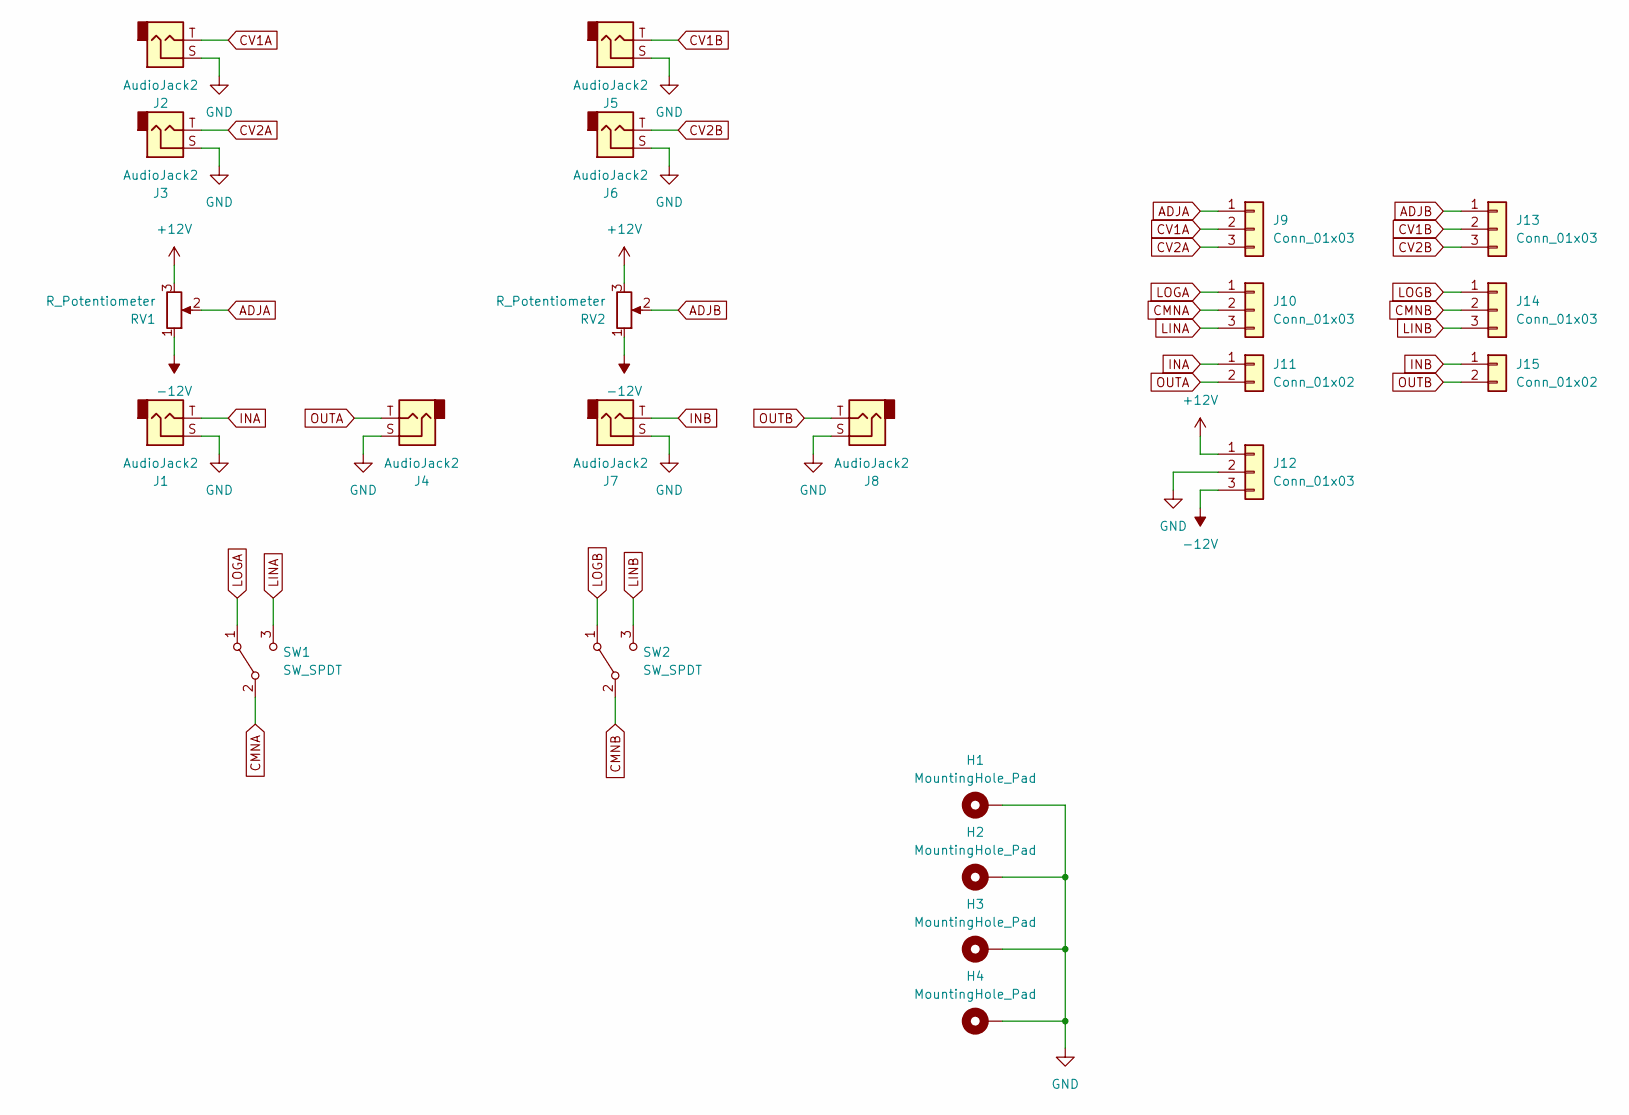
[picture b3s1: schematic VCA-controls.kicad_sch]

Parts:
H1, H2, H3, H4: MountingHole_Pad; MountingHole_3.2mm_M3_DIN965_Pad
J1, J2, J3, J4, J5, J6, J7, J8: AudioJack2; Jack_3.5mm_QingPu_WQP-PJ398SM_Vertical_CircularHoles
J9, J10, J12, J13, J14: Conn_01x03; PinHeader_1x03_P2.54mm_Vertical
J11, J15: Conn_01x02; PinHeader_1x02_P2.54mm_Vertical
RV1, RV2: R_Potentiometer; Potentiometer_Bourns_PTV09A-1_Single_Vertical
SW1, SW2: SW_SPDT; ToggleSwitch_MTS-102_SPDT

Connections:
+12V: J12.1, RV1.3, RV2.3
-12V: J12.3, RV1.1, RV2.1
ADJA: J9.1, RV1.2
ADJB: J13.1, RV2.2
CMNA: J10.2, SW1.2 (B)
CMNB: J14.2, SW2.2 (B)
CV1A: J2.T, J9.2
CV1B: J5.T, J13.2
CV2A: J3.T, J9.3
CV2B: J6.T, J13.3
GND: H1.1, H2.1, H3.1, H4.1, J1.S, J2.S, J3.S, J4.S, J5.S, J6.S, J7.S, J8.S, J12.2
INA: J1.T, J11.1
INB: J7.T, J15.1
LINA: J10.3, SW1.3 (C)
LINB: J14.3, SW2.3 (C)
LOGA: J10.1, SW1.1 (A)
LOGB: J14.1, SW2.1 (A)
OUTA: J4.T, J11.2
OUTB: J8.T, J15.2

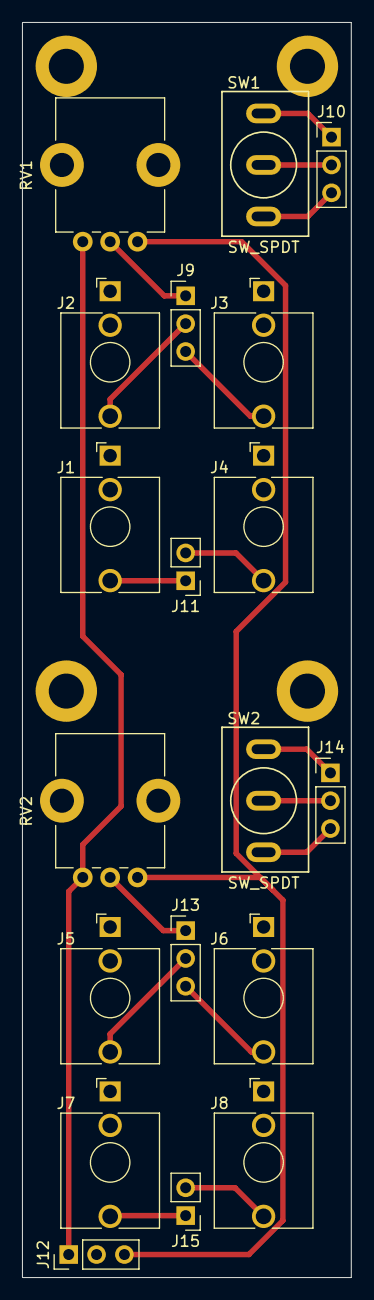
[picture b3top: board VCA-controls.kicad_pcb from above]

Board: 2 copper layers, 30.0 x 114.5 mm, 23 parts (0 on the bottom side), 19 nets.
